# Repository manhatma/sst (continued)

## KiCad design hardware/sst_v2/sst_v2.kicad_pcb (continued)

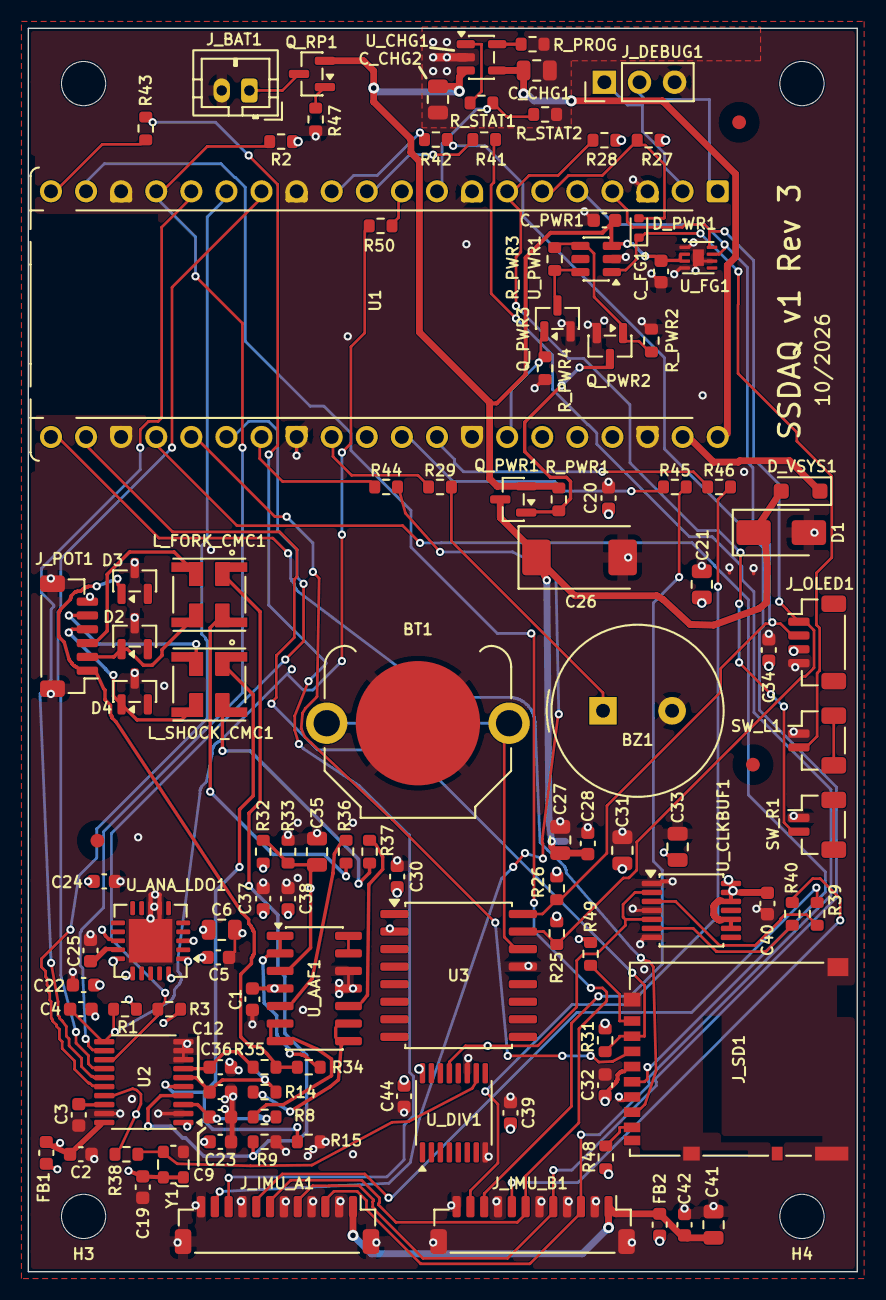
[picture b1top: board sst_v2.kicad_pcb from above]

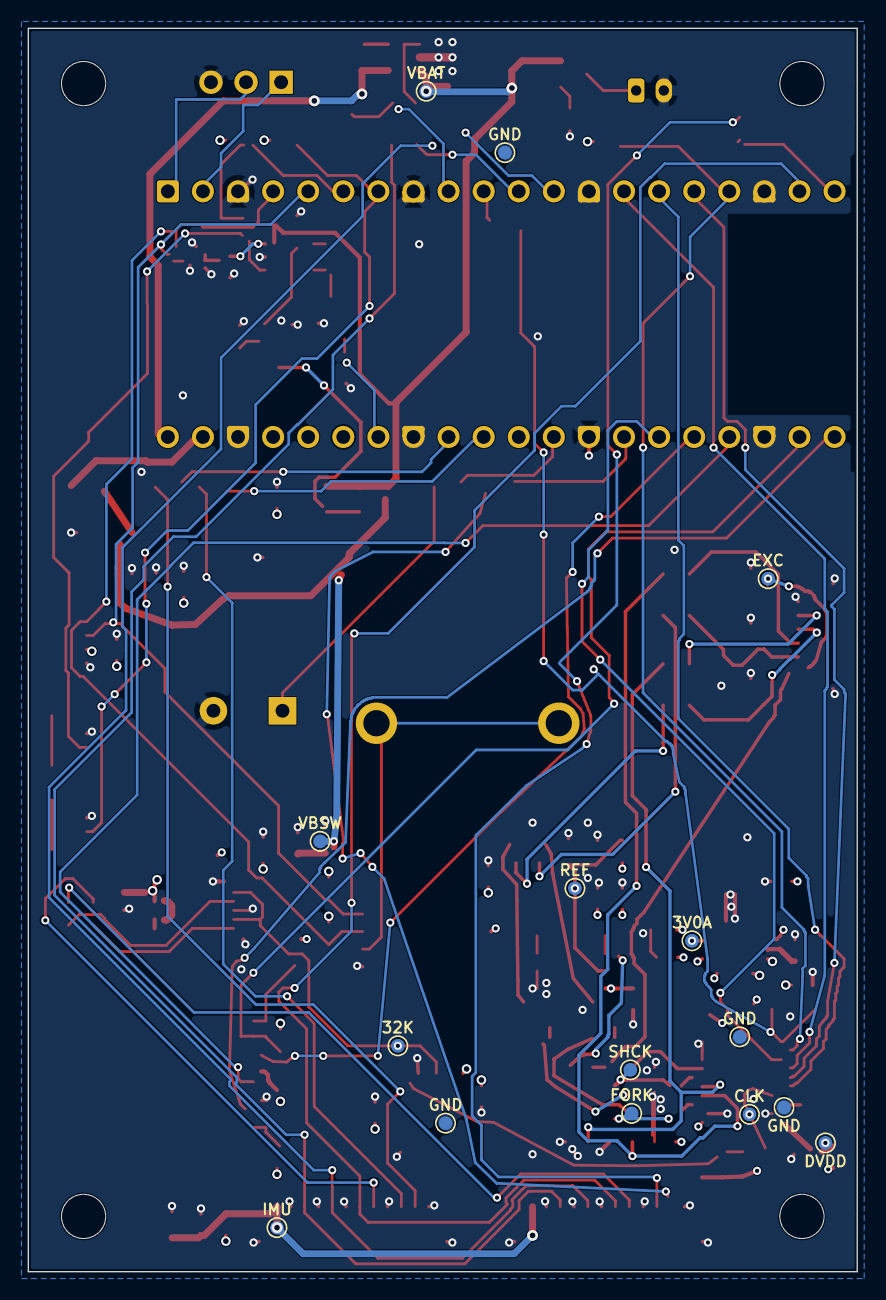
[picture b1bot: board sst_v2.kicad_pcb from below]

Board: 4 copper layers, 60.0 x 90.0 mm, 133 parts (15 on the bottom side), 82 nets.

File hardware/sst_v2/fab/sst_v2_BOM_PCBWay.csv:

Item #,Designator,Qty,Manufacturer,Mfg Part #,Description / Value,Package/Footprint,Type
1,BT1,1,Keystone,3001,"Battery holder CR1220, THT",BatteryHolder_Keystone_3001_1x12mm,THT
2,BZ1,1,TDK,PS1240P02BT,"Piezo buzzer 12 mm, 5 mm pitch, THT",Buzzer_TDK_PS1240P02BT_D12.2mm_H6.5mm,THT
3,"C2,C23,C38",3,any,,Capacitor 1uF X7R 25V 0603,0603,SMD
4,C3,1,any,,Capacitor 220nF X7R 25V 0603,0603,SMD
5,"C1,C4,C5,C19,C28,C30,C32,C34,C37,C39,C40,C42,C44,C_FG1,C_PWR1",15,any,,Capacitor 100nF X7R 50V 0603,0603,SMD
6,C6,1,any,,"Capacitor 22uF X7R 10V 0805 (LDO output, >=10 uF effective at 3 V)",0805,SMD
7,C22,1,any,,Capacitor 10uF X5R 10V 0603 (LDO input),0603,SMD
8,"C27,C31,C33,C35,C41",5,any,,Capacitor 10uF X7R 16V 0805,0805,SMD
9,"C9,C12,C20,C24,C25,C36",6,any,,Capacitor 10nF C0G 50V 0603,0603,SMD
10,C21,1,any,,Capacitor 4.7uF X7R 16V 0805,0805,SMD
11,C26,1,KEMET,T520D107M010ATE040,"Polymer tantalum 100 uF 10 V, case D (7343-31)",CP_EIA-7343-31_Kemet-D,SMD
12,"C_CHG1,C_CHG2",2,any,,Capacitor 4.7uF X5R 16V 0805 (Lader VBUS/VBAT),0805,SMD
13,D1,1,Littelfuse,SMAJ5.0CA,"TVS 5 V bidirectional, SMA",D_SMA,SMD
14,D2-D4,3,Nexperia,"PESD5V0S2BT,215","ESD protection 5 V, bidirectional double, low leakage, SOT-23 (pin 1 = line, pin 3 = GND, pin 2 unused)",SOT-23,SMD
15,D_PWR1,1,Nexperia,"RB751S40,115","Schottky 40 V 120 mA, low leakage, SOD-523 (BTN_L -> PWR_BTN)",D_SOD-523,SMD
16,D_VSYS1,1,Nexperia,"PMEG3020EH,115","Schottky 30 V 2 A, SOD-123F (blocks USB VBUS backfeed into LiPo)",D_SOD-123F,SMD
17,"FB1,FB2",2,Murata,BLM18PG471SN1D,"Ferrite bead 470 R @100 MHz, 0603",0603,SMD
18,J_BAT1,1,JST,B2B-PH-K-S(LF)(SN),"JST PH 2-pin vertical, THT",JST_PH_B2B-PH-K_1x02_P2.00mm_Vertical,THT
19,J_DEBUG1,1,generic,PinHeader 1x3 2.54 mm,"Male pin header 1x3 (UART RX/TX/GND), 2.54 mm, vertical, THT",PinHeader_1x03_P2.54mm_Vertical,THT
20,J_IMU_A1,1,JST,BM12B-SRSS-TB(LF)(SN),"JST SH 12-pin vertical, SMD",JST_SH_BM12B-SRSS-TB_1x12-1MP_P1.00mm_Vertical,SMD
21,J_IMU_B1,1,JST,BM12B-SRSS-TB(LF)(SN),"JST SH 12-pin vertical, SMD",JST_SH_BM12B-SRSS-TB_1x12-1MP_P1.00mm_Vertical,SMD
22,J_OLED1,1,JST,BM04B-SRSS-TB(LF)(SN),"JST SH 4-pin vertical, SMD",JST_SH_BM04B-SRSS-TB_1x04-1MP_P1.00mm_Vertical,SMD
23,J_POT1,1,JST,BM06B-SRSS-TB(LF)(SN),"JST SH 6-pin vertical, SMD",JST_SH_BM06B-SRSS-TB_1x06-1MP_P1.00mm_Vertical,SMD
24,J_SD1,1,Hirose,DM3AT-SF-PEJM5,"microSD socket, push-push",microSD_HC_Hirose_DM3AT-SF-PEJM5,SMD
25,"L_FORK_CMC1,L_SHOCK_CMC1",2,Murata,DLW5BTM251SQ2L,"Common-mode choke 250 R @100 MHz, 5 A",L_CommonModeChoke_Murata_DLW5BTMxxxSQ2x_5x5mm,SMD
26,"Q_PWR2,Q_PWR3",2,Diodes Inc.,2N7002-7-F,"N-MOSFET 60 V, SOT-23 (Soft-Power Gate-Treiber / PWR_OFF)",SOT-23,SMD
27,"Q_RP1,Q_PWR1",2,Diodes Inc.,DMG2305UX-7,"P-MOSFET -20 V, SOT-23 (Q_RP1 LiPo-Verpolschutz, Q_PWR1 Soft-Power-Schalter)",SOT-23,SMD
28,"R1-R3,R27,R28,R31,R47,R_STAT1",8,any,,Resistor 10k 1% 0603,0603,SMD
29,"R8,R14,R35-R37",5,any,,Resistor 1k 1% 0603,0603,SMD
30,"R9,R15",2,any,,Resistor 0R 1% 0603,0603,SMD
31,"R25,R26",2,any,,Resistor 4.7k 1% 0603,0603,SMD
32,"R29,R34",2,any,,Resistor 47R 1% 0603,0603,SMD
33,R32,1,Susumu,RG1608P-203-B-T5,"Resistor 20k 0.1% thin film, 0603",0603,SMD
34,R33,1,Susumu,RG1608P-103-B-T5,"Resistor 10k 0.1% thin film, 0603",0603,SMD
35,R38-R46,9,any,,Resistor 33R 1% 0603,0603,SMD
36,"R48,R49",2,any,,Resistor 47k 1% 0603 (microSD DAT1/DAT2 pull-up),0603,SMD
37,R50,1,any,,Resistor 100R 1% 0603 (ADC_RST-Serienwiderstand),0603,SMD
38,R_PROG,1,any,,Resistor 3.3k 1% 0603 (Ladestrom 300 mA),0603,SMD
39,R_PWR1-R_PWR4,4,any,,"Resistor 100k 1% 0603 (Soft-Power: Gate-Pull-up, Pull-downs, CLR-Pull-up)",0603,SMD
40,R_STAT2,1,any,,Resistor 10k 1% 0603 (CHG_STAT-Teiler),0603,SMD
41,SW_L1,1,JST,BM02B-SRSS-TB(LF)(SN),"JST SH 2-pin vertical, SMD",JST_SH_BM02B-SRSS-TB_1x02-1MP_P1.00mm_Vertical,SMD
42,SW_R1,1,JST,BM02B-SRSS-TB(LF)(SN),"JST SH 2-pin vertical, SMD",JST_SH_BM02B-SRSS-TB_1x02-1MP_P1.00mm_Vertical,SMD
43,U1,2,Samtec (or equivalent),SSW-120-01-T-S,"Female socket header 1x20, 2.54 mm, 8.5 mm, THT - 2 pcs per board for Raspberry Pi Pico 2 W (Pico NOT supplied/assembled)",RaspberryPi_Pico_Common_THT,THT
44,U2,1,Texas Instruments,ADS131M04IPWR,"ADC 24-bit 4-ch, TSSOP-20",TSSOP-20_4.4x6.5mm_P0.65mm,SMD
45,U3,1,Analog Devices / Maxim,DS3231SN#,"RTC, SOIC-16W",SOIC-16W_7.5x10.3mm_P1.27mm,SMD
46,U_AAF1,1,Texas Instruments,TLV4333IDR,"Quad op-amp, SOIC-14",SOIC-14_3.9x8.7mm_P1.27mm,SMD
47,U_ANA_LDO1,1,Texas Instruments,TPS7A4700RGWR,"LDO, VQFN-20 (RGW)",Texas_RGW0020A_VQFN-20-1EP_5x5mm_P0.65mm_EP3.15x3.15mm,SMD
48,U_CHG1,1,Microchip,MCP73831T-2ACI/OT,"Li-Po charger 4.20 V, SOT-23-5",SOT-23-5,SMD
49,U_CLKBUF1,1,Nexperia,"74LVC125APW,118","Quad buffer, TSSOP-14",TSSOP-14_4.4x5mm_P0.65mm,SMD
50,U_DIV1,1,Nexperia,"74HC4040PW,118","12-stage counter, TSSOP-16",TSSOP-16_4.4x5mm_P0.65mm,SMD
51,U_FG1,1,Analog Devices / Maxim,MAX17048G+T10,"Fuel Gauge 1S Li+, I2C 0x36, TDFN-8 2x2 mm EP",TDFN-8-1EP_2x2mm_P0.5mm_EP0.8x1.2mm,SMD
52,U_PWR1,1,Analog Devices / Maxim,MAX16150AUT+T,"Pushbutton On/Off Controller, 50 ms / 8 s, SOT-23-6",SOT-23-6,SMD
53,Y1,1,ECS,ECS-2520MVLC-081.92-BN-TR,"Oscillator 8.192 MHz CMOS, 2.5x2.0 mm",Oscillator_SMD_ECS_2520MV-xxx-xx-4Pin_2.5x2.0mm,SMD

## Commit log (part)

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2025-05-27 Several changes in GUI and backend
    Removed second y-axis in wheel travel diagram.
    Flipped x- with y-axis in travel histograms.
    Increased the number of bins in travel histograms.
    Changed x-axis from absolute to relative travel in travel histograms.
    Added marker and textboxes with statistical data (avg, 95th percentile, max) in travel and speed histograms.
    Replaced Savitzky-Golay filter with Whittaker-Henderson smoothing to better preserve amplitudes of narrow peaks.
2025-05-27 [Fw] Added driver for ads1115 adc
2025-05-27 [Fw] Added support for ads1115
2025-05-27 Modified sinc smoother
2025-05-27 dashboard with changes
2025-06-08 Revert "Modified sinc smoother" due to unreasonable peaks at boundaries.
    This reverts commit f841112ade7826f210f66392fd1bfa69dac6669a.
2025-06-08 Optimized WH_LAMBDA based on parameter study
    wh_lambda max. comp. velocity (mm/s) 95th percentile comp. velocity (mm/s)
    14600 2857 692
    380 5299 1168
    130 5657 1226
    100 5793 1249
    75 5995 1275
2025-06-09 WH_LAMBDA re-estimated to match the desired smoothing characteristics.
    All comments translated from German to English for clarity and consistency across the codebase.
2025-06-09 Added missing }
2025-06-14 Some minor gui modifications and comment rearrangements
2025-06-15 Changed comments to englisch
2025-07-12 [ui] changed springrate diagram layout
2025-07-28 [ui] finer resolution for speed histogram
2025-08-02 [ui] Parameter Tuning
2025-08-02 [dashboard] Added missing main.js
2026-02-15 verschiedene Änderungen
2026-02-15 [fw] extended debouncing
2026-02-15 [fw] adaption to 2x ads1115
2026-02-15 [fw] sample rate set to 860 sps
2026-02-15 [fw] customization
2026-02-15 [fw-test] teraranger evo mini implementation
2026-02-15 [fw-test] adaption for teraranger evo mini
2026-02-15 [fw-test] teraranger evo mini driver
2026-02-15 [ui] travel hist. comparison chart added
2026-02-15 [ui] some change
2026-02-15 [ui] added switch for relative and absolute unit in travel hist. comp.
2026-02-16 [ui] fixed "Invalid range" when box select
2026-03-08 Add VolSpc support and travel comparison improvements
2026-03-08 layout: fill vertical space for LR/SW charts and notes panel
    - Switch Leverage Ratio and Shock-Wheel displacement Bokeh figures
    to sizing_mode='stretch_both' with min_height=255 so they expand
    to fill available grid-cell height instead of leaving empty space.
    - Remove fixed min-height from .description-box and set height:100%
    so the notes panel always fills its grid row.
    - Add height:100% to .lr, .sw, .description wrapper elements and
2026-03-08 feat: add velocity balance comparison to Travel hist. comp. tab
    Split the comparison tab into two 50/50 columns:
    - Left: existing travel histogram comparison + FFT comparison (unchanged)
    - Right: new combined velocity balance comparison figure
    The new figure shows compression and rebound trendlines (lines only,
    no scatter dots) in a single chart with a horizontal zero-line divider.
    Compression trendlines sit in Q1 (positive velocity), rebound trendlines
2026-03-08 Fix chart x-axis label clipping in dashboard tabs
2026-04-24 fix: forward-declare SNTP time hooks for gcc 14+
    Newer arm-none-eabi toolchains (gcc 14/15) treat implicit function
    declarations as errors, so lwIP's sntp.c failed to compile because
    the SNTP_GET_SYSTEM_TIME / SNTP_SET_SYSTEM_TIME_US macros reference
    get_system_time_us and set_system_time_us without having seen a
    prototype. Add explicit prototypes next to the macro definitions.
2026-04-24 feat: RTC sync via iPhone over local TCP
    Add STATUS_TIME_SYNC (code 7) to the DAQ's TCP protocol so the iOS
    app can push its current UTC epoch to the DAQ whenever they share
    an access point, without the DAQ needing internet access.
    On receipt, the 8-byte int64 payload is passed to set_system_time_us()
    which updates both the Pico-internal RTC and the battery-backed
    DS3231. The server acknowledges with STATUS_TIME_SYNCED (code 11)
2026-05-08 fix: force shock-wheel polynomial through origin
    Unconstrained least-squares left a non-zero constant term in the 3rd-order
    fit, biasing every rear-travel sample by coeffs[0] so the signal never
    returned to 0 even when the shock was fully extended (airtime). The
    calibration defines Wheel(shock=0)=0 as a hard physical constraint, so
    zero out coeffs[0] after the fit. Bumps CurrentProcessingVersion.
2026-05-09 fw: show board ID on idle screen, confirm TCP serve auto-exit
    Two related firmware extensions that complete the BOARDID feature and the
    auto-exit pipeline that Sufni.Bridge already implements on its side.
    Board-ID display:
    - boardid_current_id() loads the unique board identifier from the BOARDID
    file on the SD card (separate from the BOARDID.CUR suffix which selects
    the calibration template). Loaded in boardid_apply() and
